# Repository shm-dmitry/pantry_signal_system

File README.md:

This is signal system for pantry.
It will control climate of pantry to smart house.

It will uses autonomous power system
1. car battery on 12v
2. temporary Li-Ion battary on 12v for charging primary battery
3. internal battery (6V..15V) which will used in case of primary and reserve 12V battery discharged. Used to send power alarm to smart house
4. Auto battary hot switch
5. Control over-discharge of all batteries
6. Provide information of current voltage to controller
7. Small current consumption. I plan to charge main battary once per ~6 month. 

It will collect and send next information (incl alarms):
1. Inside flooding alarm
2. Outside flooding alarm
3. Inside humidity level
4. Inside temperature
5. Inside light level
6. Open door alarm
7. Current voltage of all batteries
8. Current battery in use
9. Both 12V batteries discharged alarm 

It will automatically switch on air-drier basing on humidity level

It will have air fan system
1. Manual swotch on
2. Manual swotch off
3. Auto switch off after ~20 minutes

It will send all collected information to smart house system using LoRa channel

Project status

| Hardware | Status |
| --- | --- |
| Supply module | OK |
| Supply module :: Supply controller | OK |
| Logic module :: Flooding sensors | OK |
| Logic module :: Light sensor | OK |
| Logic module :: display | OK |
| Logic module :: humidity and temperature | OK |
| Logic module :: air dryer | OK |
| Logic module :: LoRa transmitter | OK |
| Logic module :: Open door alarm | OK |
| Logic module :: Wakeup button | OK |
| Air fan module | OK |
| LoRa receiver and smart house integration | OK |

| Firmware | Status |
| --- | --- |
| Supply controller | OK |
| Logic controller :: flooding sensors | OK |
| Logic controller :: light sensor | OK |
| Logic controller :: display | OK |
| Logic controller :: humidity and temperature | OK |
| Logic controller :: air dryer | OK |
| Logic controller :: LoRa transmitter | OK |
| Logic controller :: Open door alarm | OK |
| Logic controller :: Wakeup button and deep sleep mode | OK |
| Logic controller :: Integration with supply controller | OK |
| LoRa receiver and smart house integration | OK |

| Board | Status |
| --- | --- |
| Supply board | OK |
| logic module board | OK |
| fan board | OK |
| LoRa Receiver | OK |

| 3D models | Status |
| --- | --- |
| Supply board box | OK |
| Logic model box | OK |
| Air dryer | OK |
| Fan box | OK |
| Fan air intake | OK |
| LoRa receiver box | no |

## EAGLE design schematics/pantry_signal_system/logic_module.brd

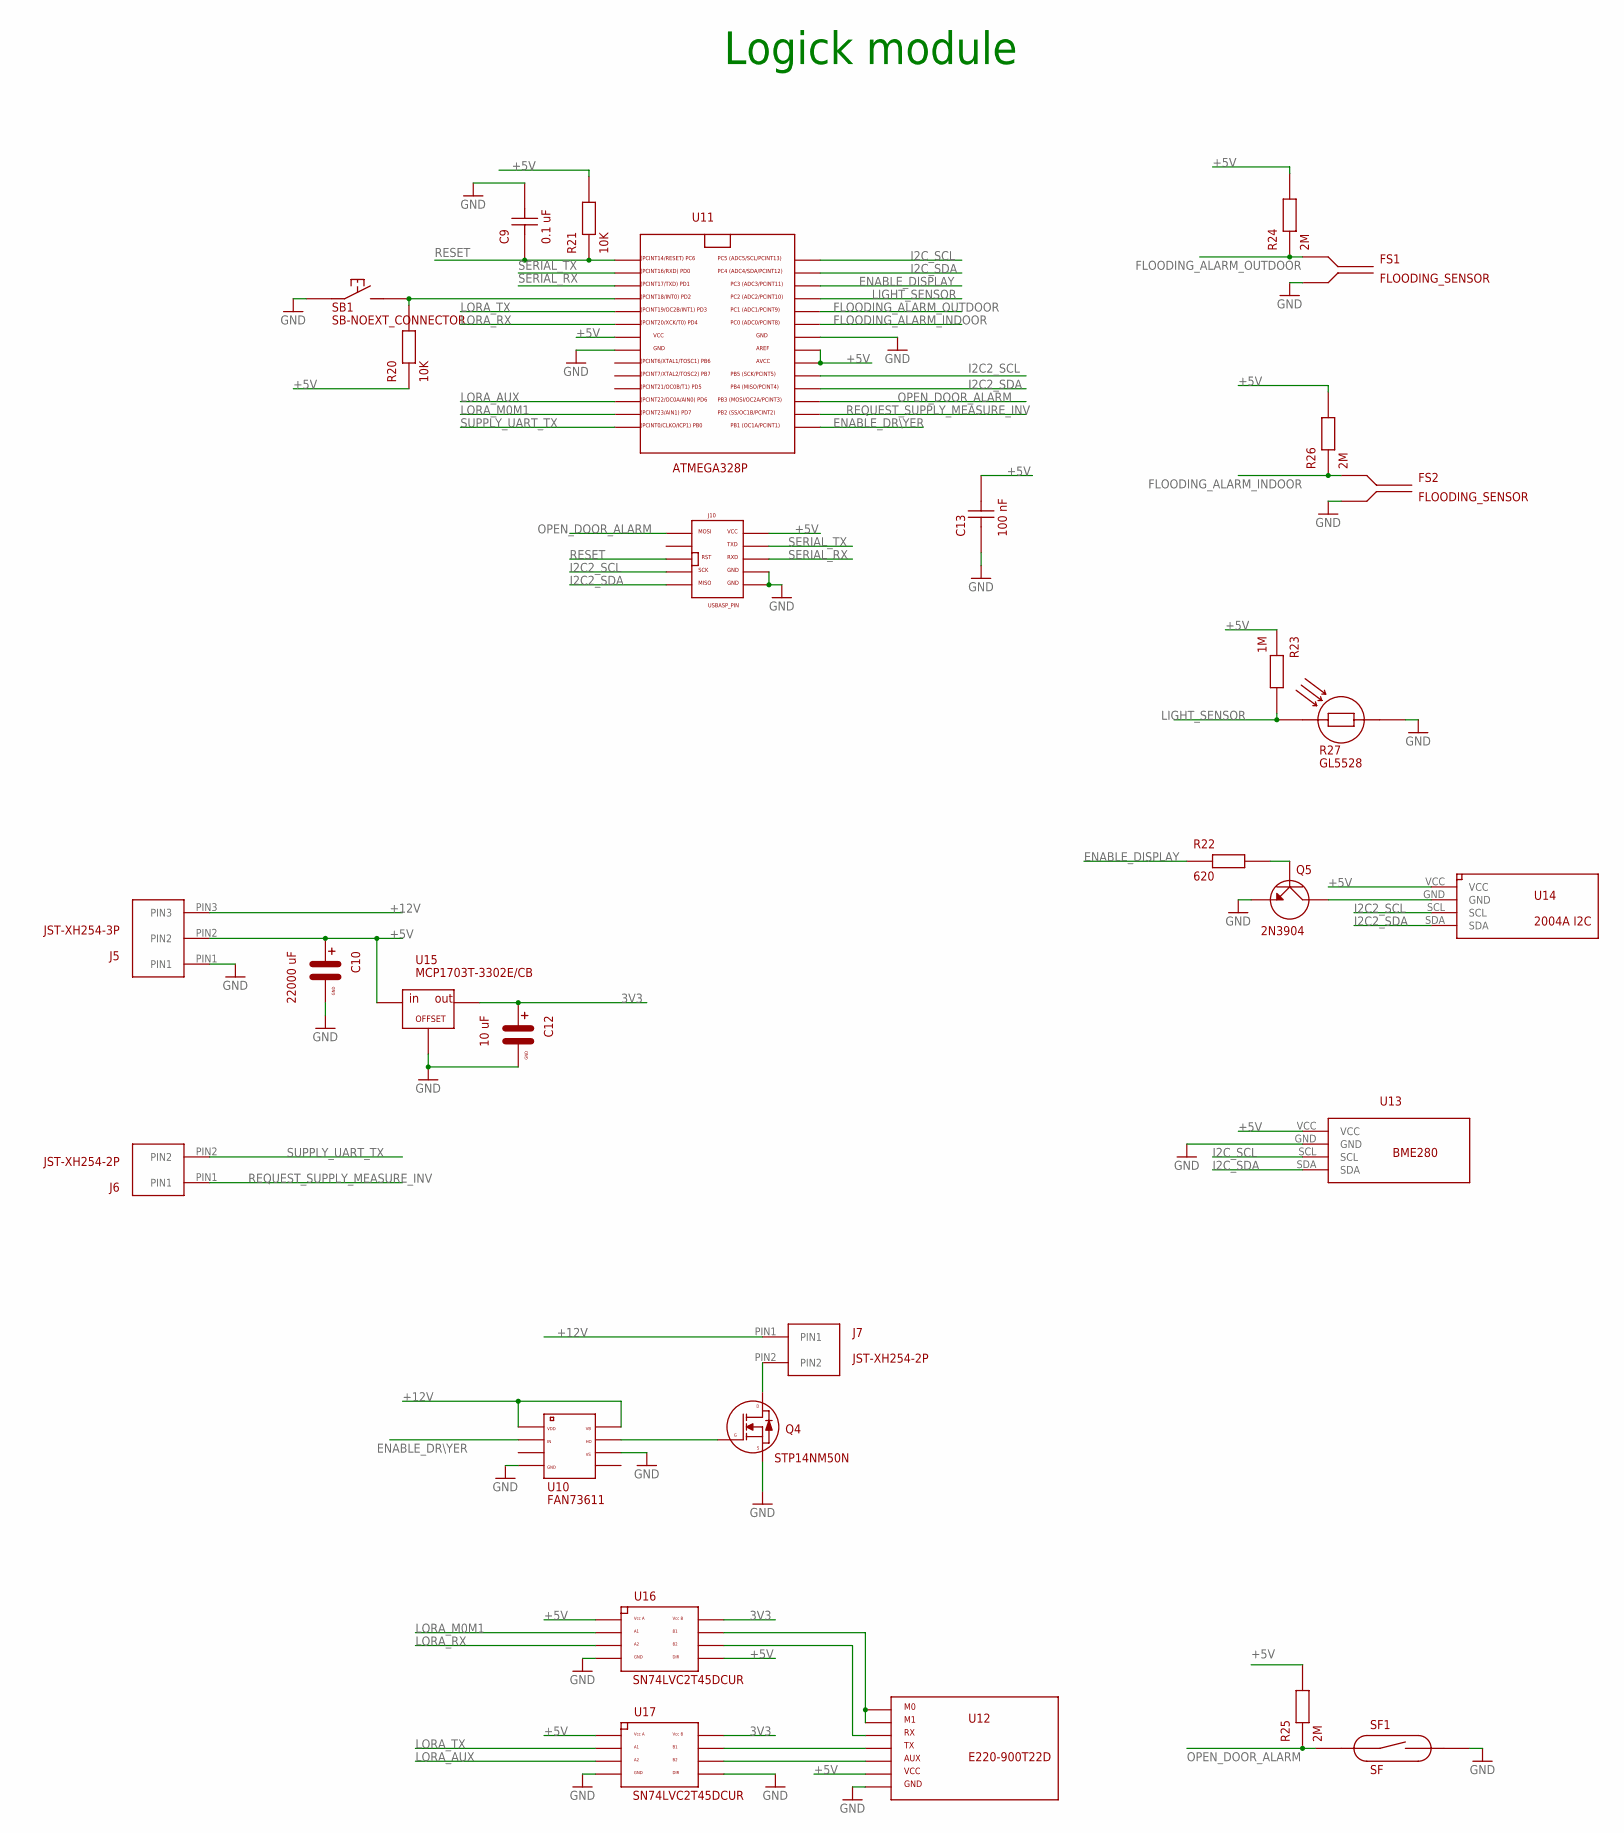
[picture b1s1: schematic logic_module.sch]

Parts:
C9: 0.1 uF; C-1
C10: 22000 uF; C-MINI-5X7
C12: 10 uF; C-MINI-5X7
C13: 100 nF; C-1
FS1, FS2: FLOODING_SENSOR
J5: JST-XH254-3P
J6, J7: JST-XH254-2P
J10: USBASP_PIN
Q4: STP14NM50N; MOSFET_N
Q5: 2N3904; TRANSISTOR
R20, R21: 10K; R
R22: 620; R
R23: 1M; R
R24, R25, R26: 2M; R
R27: GL5528; RF
SB1: SB-NOEXT_CONNECTOR; SB-EXT
SF1: SF
U10: FAN73611; SOIC-8
U11: ATMEGA328P
U12: E220-900T22D; LORA
U13: BME280BME280-CONNECTOR-ONLY; BME280-CONNECTOR-ONLY
U14: 2004A I2C; I2C_DISPLAY
U15: MCP1703T-3302E/CB; SOT-23A
U16, U17: SN74LVC2T45DCUR; VSSOP-8

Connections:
3V3: C12.PLUS (PIN_PLUS), U15.P2 (OUT), U16.P8 (VCCB), U17.P8 (VCCB)
+5V: C10.PLUS (PIN_PLUS), C13.P$2, J5.PIN2, J10.VCC, R20.P$1, R21.P$2, R23.P$1, R24.P$2, R25.P$2, R26.P$2, U11.AREF, U11.AVCC, U11.VCC, U12.VCC, U13.VCC, U14.VCC, U15.P3 (IN), U16.P1 (VCCA), U16.P5 (DIR), U17.P1 (VCCA)
+12V: J5.PIN3, J7.PIN1, U10.P_1 (VDD), U10.P_8 (VB)
ENABLE_DISPLAY: R22.P$1, U11.PC3
ENABLE_DR\YER: U10.P_2 (IN), U11.PB1
FLOODING_ALARM_INDOOR: FS2.P$1, R26.P$1, U11.PC0
FLOODING_ALARM_OUTDOOR: FS1.P$1, R24.P$1, U11.PC1
GND: C9.P$2, C10.MINUS (PIN_GND), C12.MINUS (PIN_GND), C13.P$1, FS1.P$2, FS2.P$2, J5.PIN1, J10.GND, J10.GND1, Q4.S, Q5.E, R27.PIN2, SB1.P$1, SF1.P$2, U10.P_4 (GND), U10.P_6 (VS), U11.GND, U11.GND1, U12.GND, U13.GND, U15.P1 (GND), U16.P4 (GND), U17.P4 (GND), U17.P5 (DIR)
I2C2_SCL: J10.SCK, U11.PB5, U14.SCL
I2C2_SDA: J10.MISO, U11.PB4, U14.SDA
I2C_SCL: U11.PC5, U13.SCL
I2C_SDA: U11.PC4, U13.SDA
LIGHT_SENSOR: R23.P$2, R27.PIN1, U11.PC2
LORA_AUX: U11.PD6, U17.P3 (A2)
LORA_M0M1: U11.PD7, U16.P2 (A1)
LORA_RX: U11.PD4, U16.P3 (A2)
LORA_TX: U11.PD3, U17.P2 (A1)
unnamed: U12.TX, U17.P7 (B1)
unnamed: U12.RX, U16.P6 (B2)
unnamed: U12.AUX, U17.P6 (B2)
unnamed: J7.PIN2, Q4.D
unnamed: Q4.G, U10.P_7 (HO)
unnamed: U12.M0, U12.M1, U16.P7 (B1)
unnamed: Q5.C, U14.GND
unnamed: Q5.B, R22.P$2
unnamed: R20.P$2, SB1.P$2, U11.PD2
OPEN_DOOR_ALARM: J10.MOSI, R25.P$1, SF1.P$1, U11.PB3
REQUEST_SUPPLY_MEASURE_INV: J6.PIN1, U11.PB2
RESET: C9.P$1, J10.RST (RESET), R21.P$1, U11.PC6
SERIAL_RX: J10.RXD, U11.PD1
SERIAL_TX: J10.TXD, U11.PD0
SUPPLY_UART_TX: J6.PIN2, U11.PB0

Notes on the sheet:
Logick module

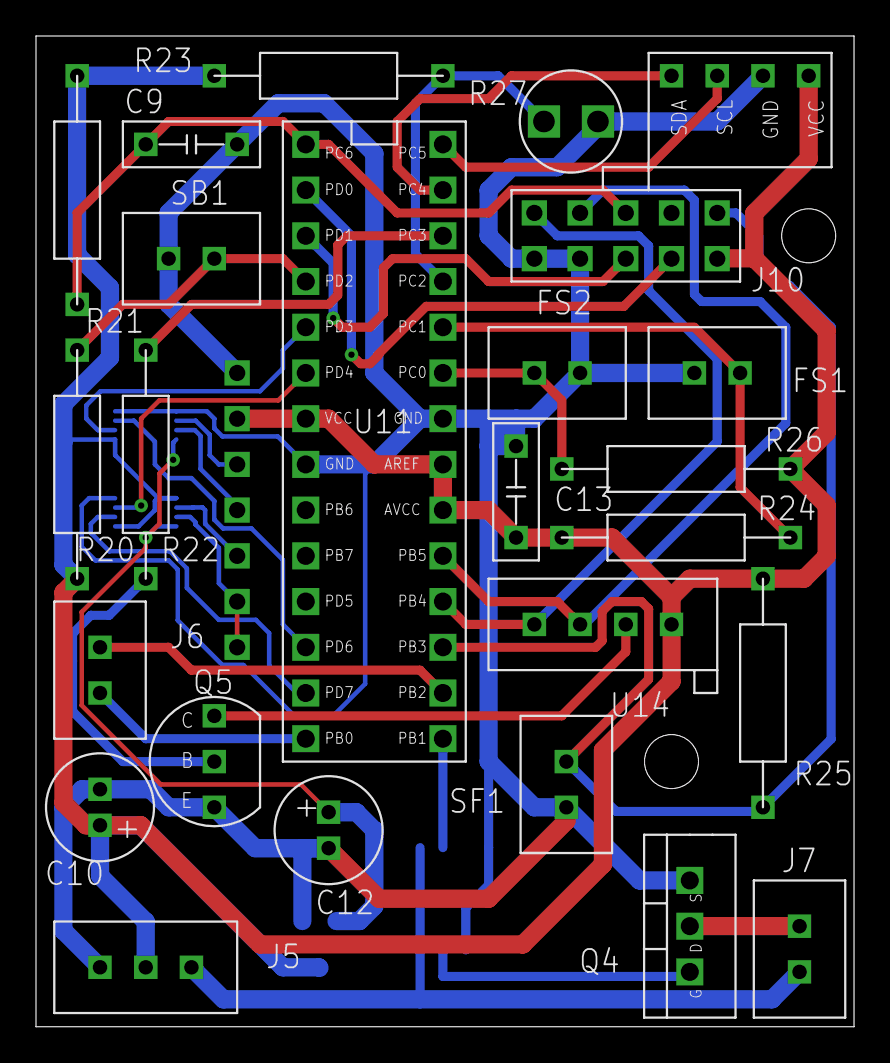
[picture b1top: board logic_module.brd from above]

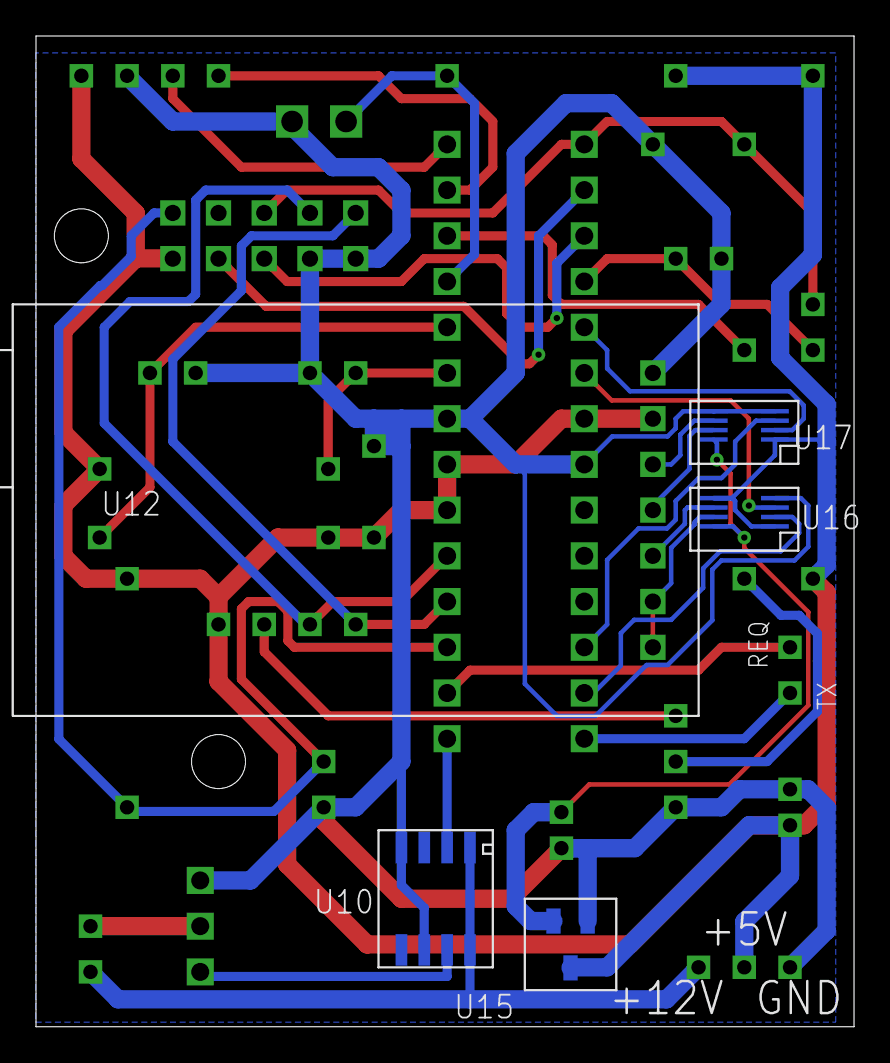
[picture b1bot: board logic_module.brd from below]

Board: 2 copper layers, 45.4 x 55.0 mm, 30 parts (5 on the bottom side), 32 nets.

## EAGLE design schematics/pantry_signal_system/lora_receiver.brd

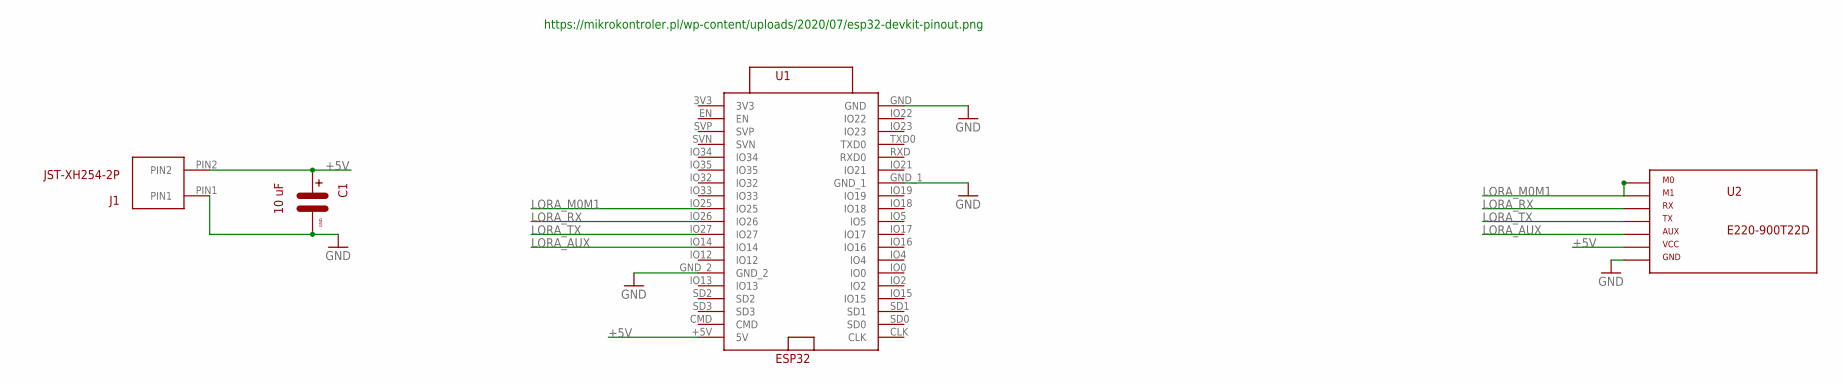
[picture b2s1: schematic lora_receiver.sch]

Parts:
C1: 10 uF; C-MINI-5X7
J1: JST-XH254-2P
U1: ESP32
U2: E220-900T22D; LORA

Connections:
3V3: U1.3V3
+5V: C1.PLUS (PIN_PLUS), J1.PIN2, U1.+5V (5V), U2.VCC
GND: C1.MINUS (PIN_GND), J1.PIN1, U1.GND, U1.GND_1, U1.GND_2, U2.GND
LORA_AUX: U1.IO14, U2.AUX
LORA_M0M1: U1.IO25, U2.M0, U2.M1
LORA_RX: U1.IO26, U2.RX
LORA_TX: U1.IO27, U2.TX

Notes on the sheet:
https://mikrokontroler.pl/wp-content/uploads/2020/07/esp32-devkit-pinout.png

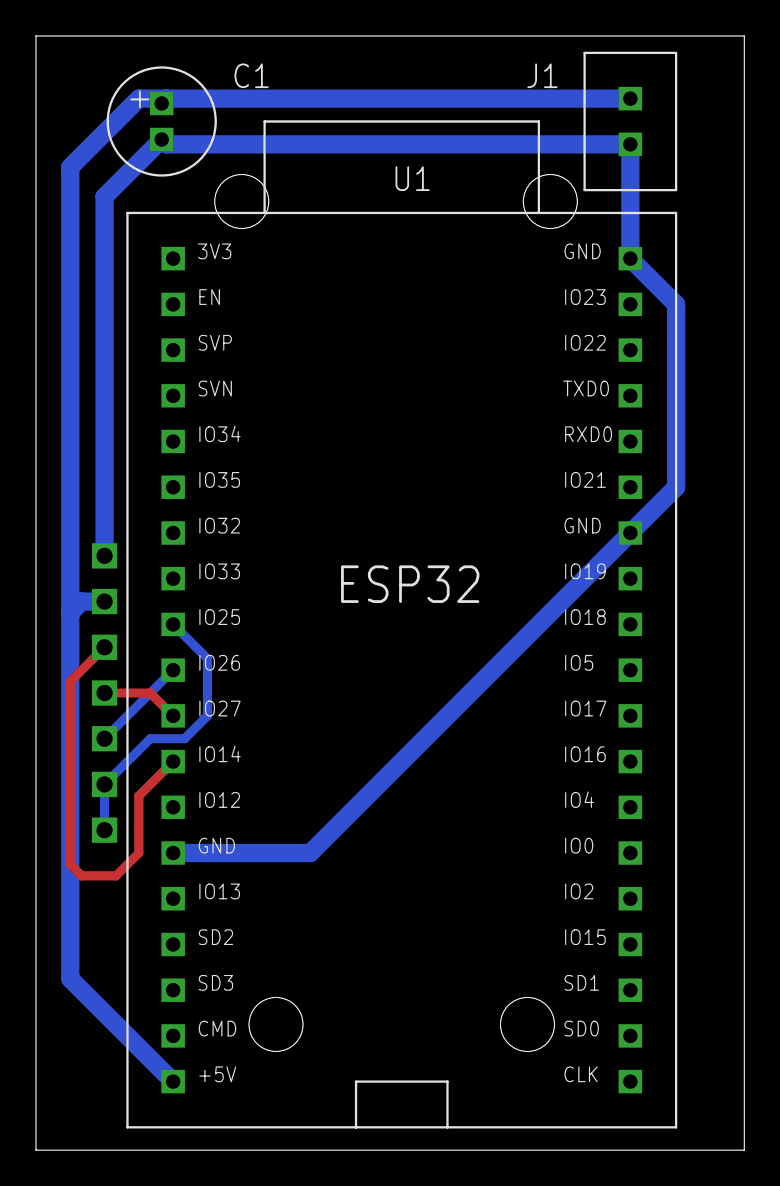
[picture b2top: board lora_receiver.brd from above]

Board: 2 copper layers, 39.4 x 61.9 mm, 4 parts (1 on the bottom side), 6 nets.

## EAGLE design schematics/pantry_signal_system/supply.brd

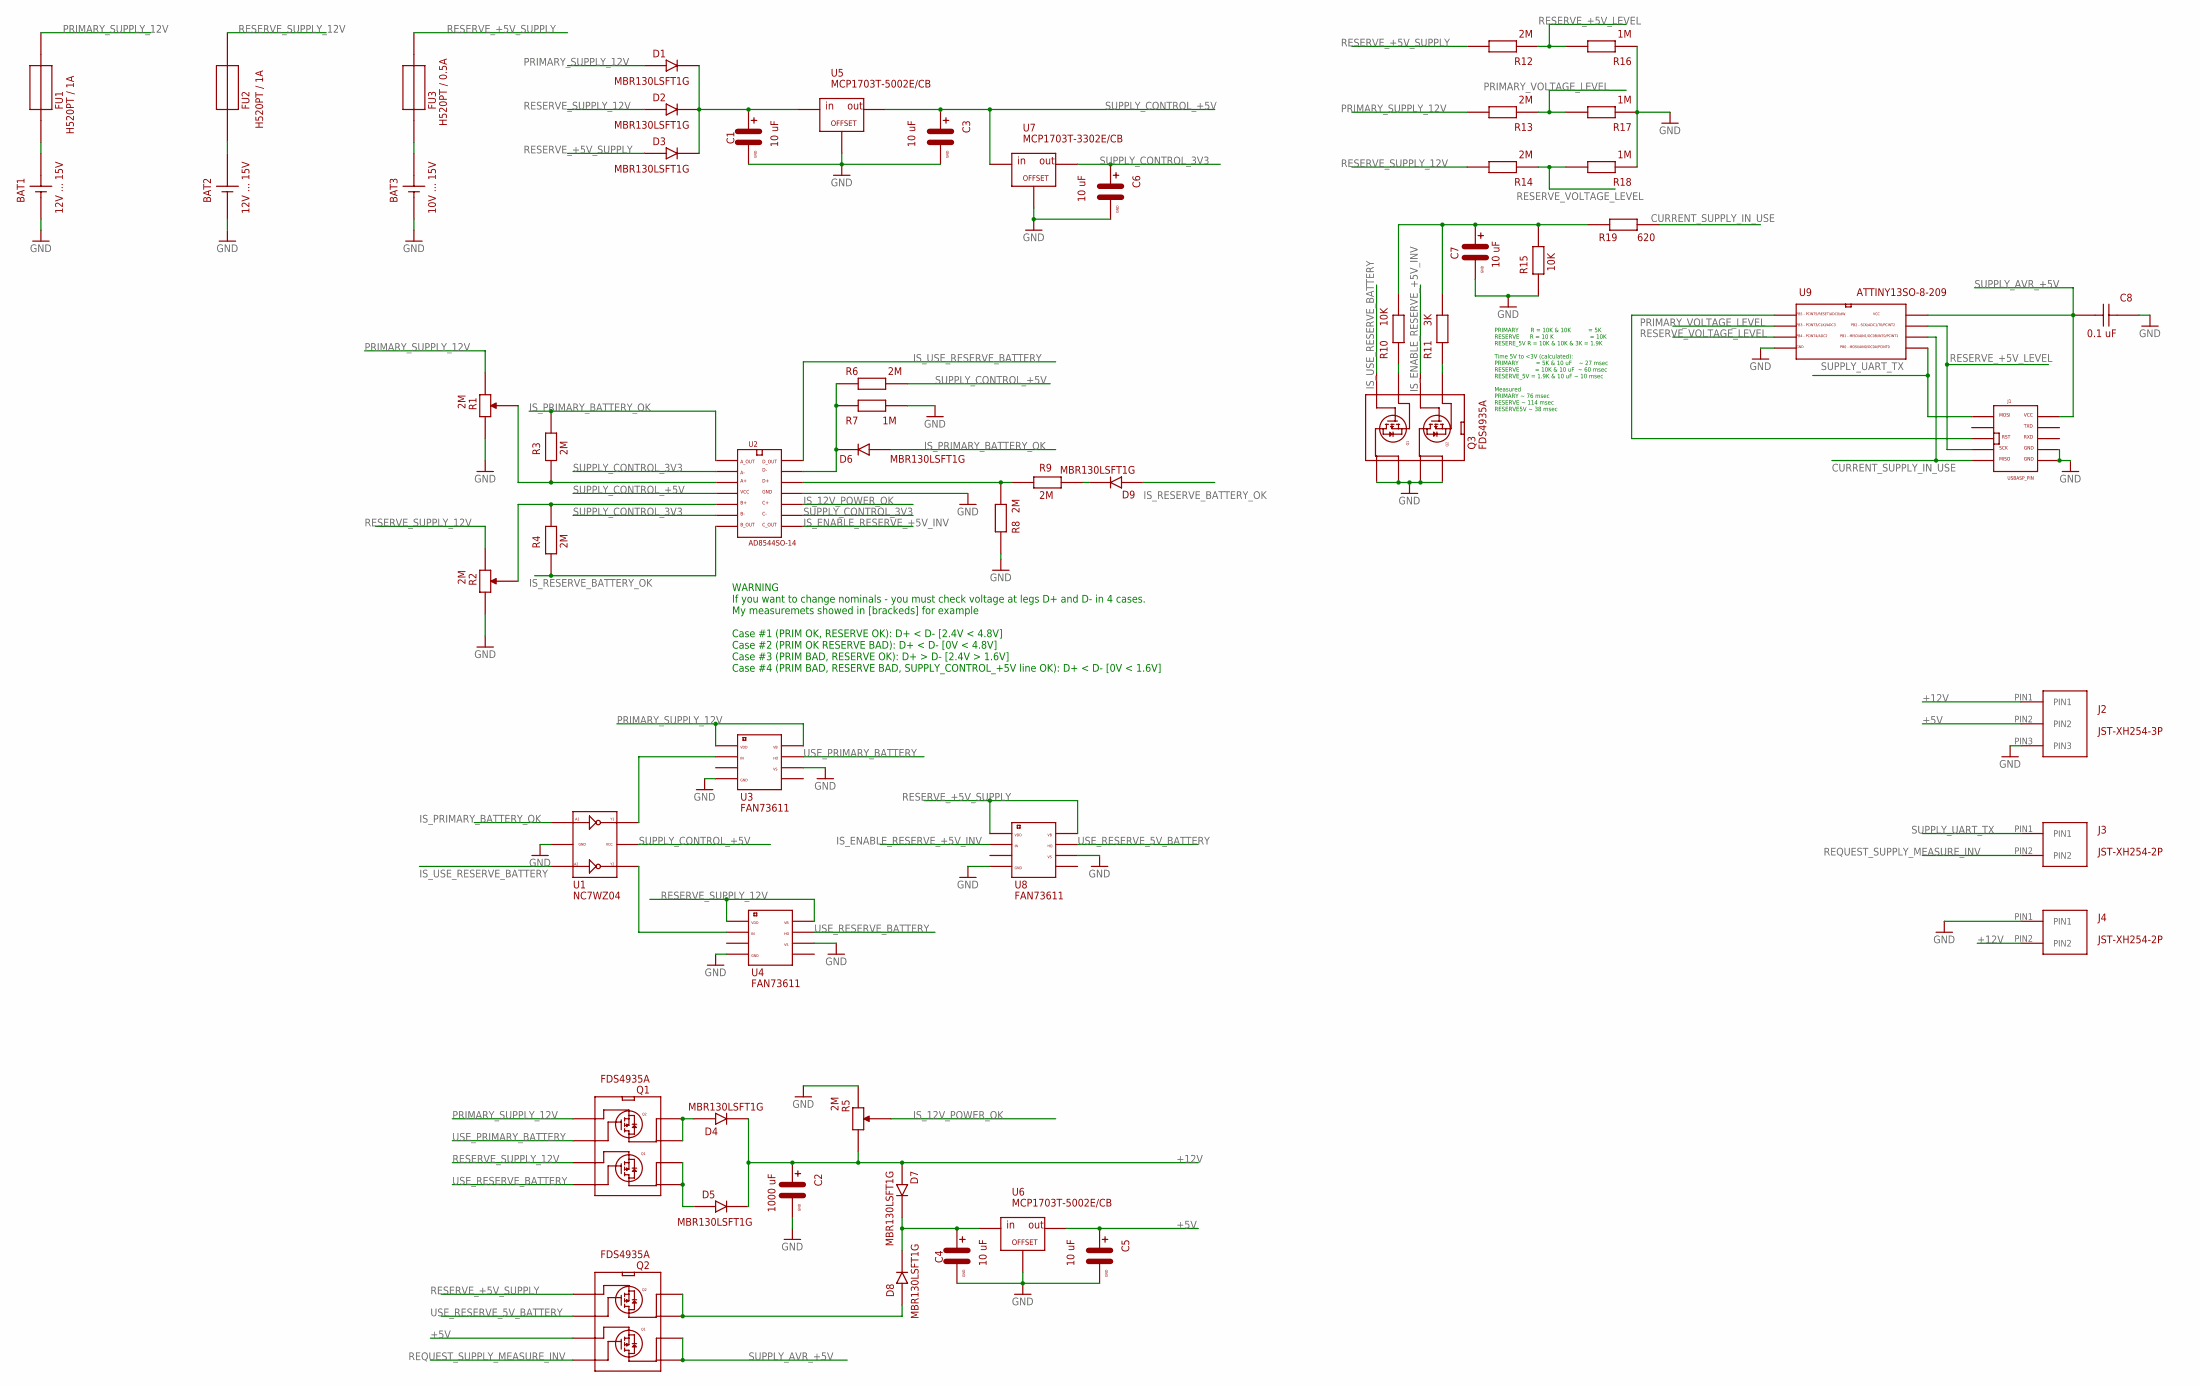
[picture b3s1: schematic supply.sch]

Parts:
BAT1, BAT2: 12V ... 15V; BATTERY
BAT3: 10V ... 15V; BATTERY
C1, C3, C4, C5, C6, C7: 10 uF; C-MINI-5X7
C2: 1000 uF; C
C8: 0.1 uF; C-1
D1, D2, D3, D4, D5, D6, D7, D8, D9: MBR130LSFT1G; D-SOD-123FL
FU1, FU2: H520PT / 1A; FU
FU3: H520PT / 0.5A; FU
J1: USBASP_PIN
J2: JST-XH254-3P
J3, J4: JST-XH254-2P
Q1, Q2, Q3: FDS4935A; SO-8
R1, R2, R5: 2M; RD-3296W-1-205LF
R3, R4, R6, R8, R9, R12, R13, R14: 2M; R
R7, R16, R17, R18: 1M; R
R10, R15: 10K; R
R11: 3K; R
R19: 620; R
U1: NC7WZ04; SC70
U2: AD8544SO-14; SO-14
U3, U4, U8: FAN73611; SOIC-8
U5, U6: MCP1703T-5002E/CB; SOT-23A
U7: MCP1703T-3302E/CB; SOT-23A
U9: ATTINY13SO-8-209; SO-8-209

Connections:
+5V: C5.PLUS (PIN_PLUS), J2.PIN2, Q2.P3 (S1), U6.P2 (OUT)
+12V: C2.PIN_PLUS, D4.CATHODE, D5.CATHODE, D7.ANODE, J2.PIN1, J4.PIN2, R5.P2
BAT1: BAT1.PLUS, FU1.P$1
BAT2: BAT2.PLUS, FU2.P$1
BAT3: BAT3.PLUS, FU3.P$1
CURRENT_SUPPLY_IN_USE: J1.MISO, R19.P$2, U9.P6 (PB1)
GND: BAT1.MINUS, BAT2.MINUS, BAT3.MINUS, C1.MINUS (PIN_GND), C2.PIN_GND, C3.MINUS (PIN_GND), C4.MINUS (PIN_GND), C5.MINUS (PIN_GND), C6.MINUS (PIN_GND), C7.MINUS (PIN_GND), C8.P$2, J1.GND, J1.GND1, J2.PIN3, J4.PIN1, Q3.P5 (D11), Q3.P6 (D12), Q3.P7 (D21), Q3.P8 (D22), R1.P2, R2.P2, R5.P1, R7.P$1, R8.P$2, R15.P$1, R16.P$1, R17.P$1, R18.P$1, U1.P2 (GND), U2.P11 (GND), U3.P_4 (GND), U3.P_6 (VS), U4.P_4 (GND), U4.P_6 (VS), U5.P1 (GND), U6.P1 (GND), U7.P1 (GND), U8.P_4 (GND), U8.P_6 (VS), U9.P4 (GND)
IS_12V_POWER_OK: R5.P3, U2.P10 (C+)
IS_ENABLE_RESERVE_+5V_INV: Q3.P2 (G2), U2.P8 (C_OUT), U8.P_2 (IN)
IS_PRIMARY_BATTERY_OK: D6.ANODE, R3.P$2, U1.P1 (A1), U2.P1 (A_OUT)
IS_RESERVE_BATTERY_OK: D9.ANODE, R4.P$1, U2.P7 (B_OUT)
IS_USE_RESERVE_BATTERY: Q3.P4 (G1), U1.P3 (A2), U2.P14 (D_OUT)
unnamed: C1.PLUS (PIN_PLUS), D1.CATHODE, D2.CATHODE, D3.CATHODE, U5.P3 (IN)
unnamed: D6.CATHODE, R6.P$2, R7.P$2, U2.P13 (D-)
unnamed: R1.P3, R3.P$1, U2.P3 (A+)
unnamed: C4.PLUS (PIN_PLUS), D7.CATHODE, D8.CATHODE, U6.P3 (IN)
unnamed: R2.P3, R4.P$2, U2.P5 (B+)
unnamed: R8.P$1, R9.P$1, U2.P12 (D+)
unnamed: D4.ANODE, Q1.P7 (D21), Q1.P8 (D22)
unnamed: D5.ANODE, Q1.P5 (D11), Q1.P6 (D12)
unnamed: J1.RST (RESET), U9.P1 (PB5)
unnamed: U1.P6 (Y1), U3.P_2 (IN)
unnamed: U1.P4 (Y2), U4.P_2 (IN)
unnamed: Q3.P3 (S1), R10.P$1
unnamed: D8.ANODE, Q2.P7 (D21), Q2.P8 (D22)
unnamed: Q3.P1 (S2), R11.P$1
unnamed: D9.CATHODE, R9.P$2
unnamed: C7.PLUS (PIN_PLUS), R10.P$2, R11.P$2, R15.P$2, R19.P$1
PRIMARY_SUPPLY_12V: D1.ANODE, FU1.P$2, Q1.P1 (S2), R1.P1, R13.P$2, U3.P_1 (VDD), U3.P_8 (VB)
PRIMARY_VOLTAGE_LEVEL: R13.P$1, R17.P$2, U9.P2 (PB3)
REQUEST_SUPPLY_MEASURE_INV: J3.PIN2, Q2.P4 (G1)
RESERVE_+5V_LEVEL: J1.SCK, R12.P$1, R16.P$2, U9.P7 (PB2)
RESERVE_+5V_SUPPLY: D3.ANODE, FU3.P$2, Q2.P1 (S2), R12.P$2, U8.P_1 (VDD), U8.P_8 (VB)
RESERVE_SUPPLY_12V: D2.ANODE, FU2.P$2, Q1.P3 (S1), R2.P1, R14.P$2, U4.P_1 (VDD), U4.P_8 (VB)
RESERVE_VOLTAGE_LEVEL: R14.P$1, R18.P$2, U9.P3 (PB4)
SUPPLY_AVR_+5V: C8.P$1, J1.VCC, Q2.P5 (D11), Q2.P6 (D12), U9.P8 (VCC)
SUPPLY_CONTROL_3V3: C6.PLUS (PIN_PLUS), U2.P2 (A-), U2.P6 (B-), U2.P9 (C-), U7.P2 (OUT)
SUPPLY_CONTROL_+5V: C3.PLUS (PIN_PLUS), R6.P$1, U1.P5 (VCC), U2.P4 (VCC), U5.P2 (OUT), U7.P3 (IN)
SUPPLY_UART_TX: J1.MOSI, J3.PIN1, U9.P5 (PB0)
USE_PRIMARY_BATTERY: Q1.P2 (G2), U3.P_7 (HO)
USE_RESERVE_5V_BATTERY: Q2.P2 (G2), U8.P_7 (HO)
USE_RESERVE_BATTERY: Q1.P4 (G1), U4.P_7 (HO)

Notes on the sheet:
PRIMARY R = 10K & 10K = 5K RESERVE R = 10 K = 10K RESERE_5V R = 10K & 10K & 3K = 1.9K Time 5V to <3V (calculated): PRIMARY = 5K & 10 uF ~ 27 msec RESERVE = 10K & 10 uF ~ 60 msec RESERVE_5V = 1.9K & 10 uF ~ 10 msec Measured PRIMARY ~ 76 msec RESERVE ~ 114 msec RESERVE5V ~ 38 msec
WARNING If you want to change nominals - you must check voltage at legs D+ and D- in 4 cases. My measuremets showed in [brackeds] for example Case #1 (PRIM OK, RESERVE OK): D+ < D- [2.4V < 4.8V] Case #2 (PRIM OK RESERVE BAD): D+ < D- [0V < 4.8V] Case #3 (PRIM BAD, RESERVE OK): D+ > D- [2.4V > 1.6V]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

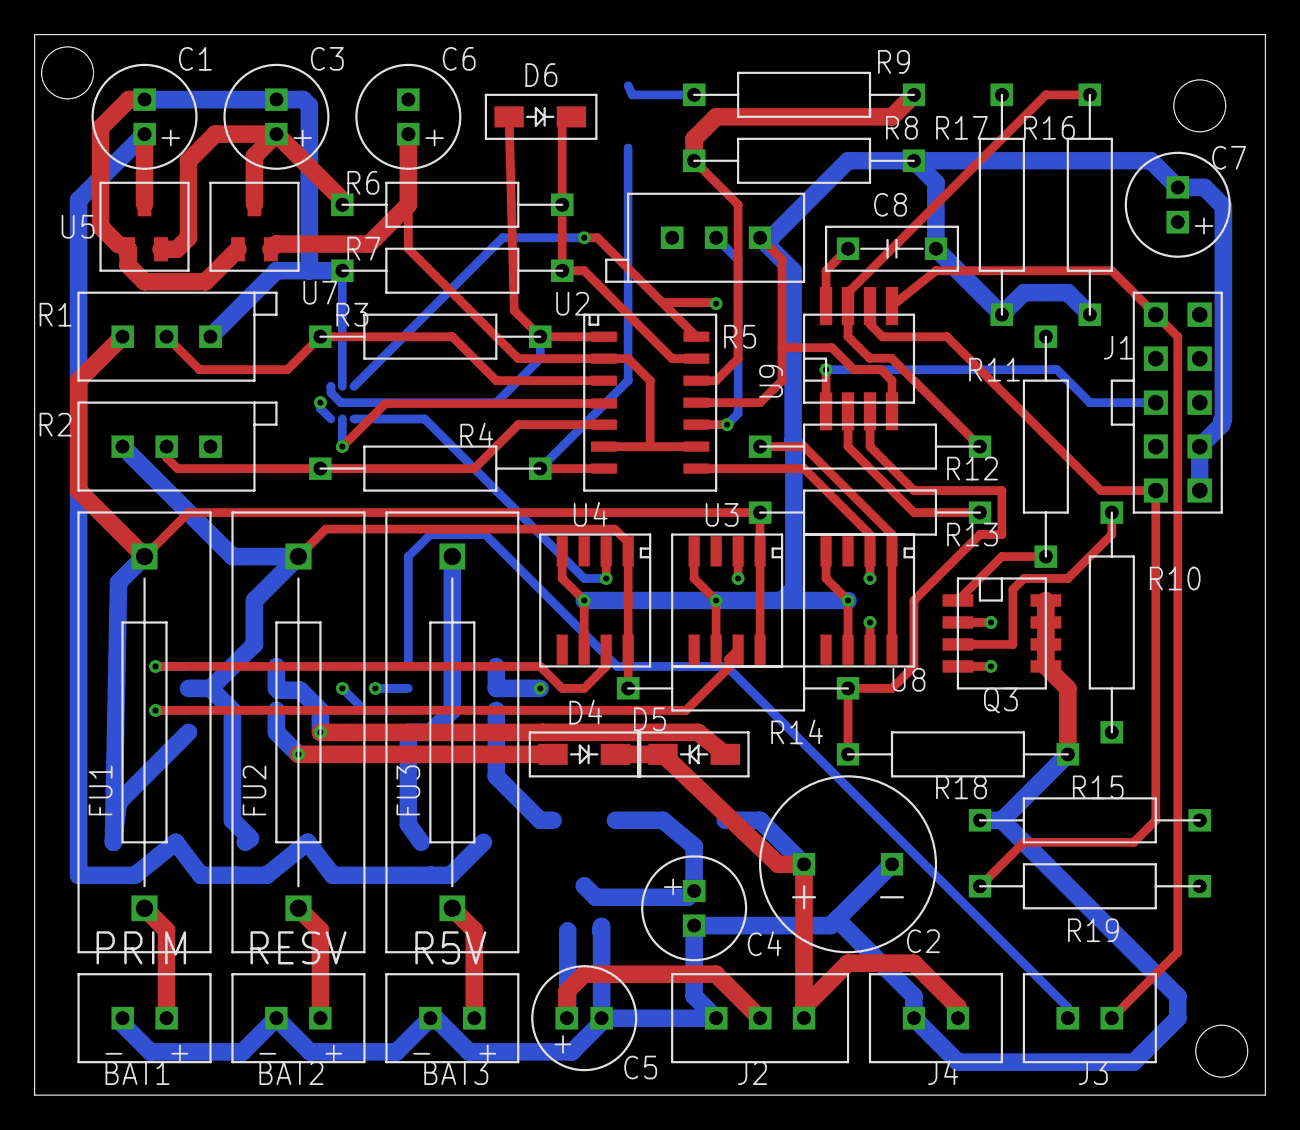
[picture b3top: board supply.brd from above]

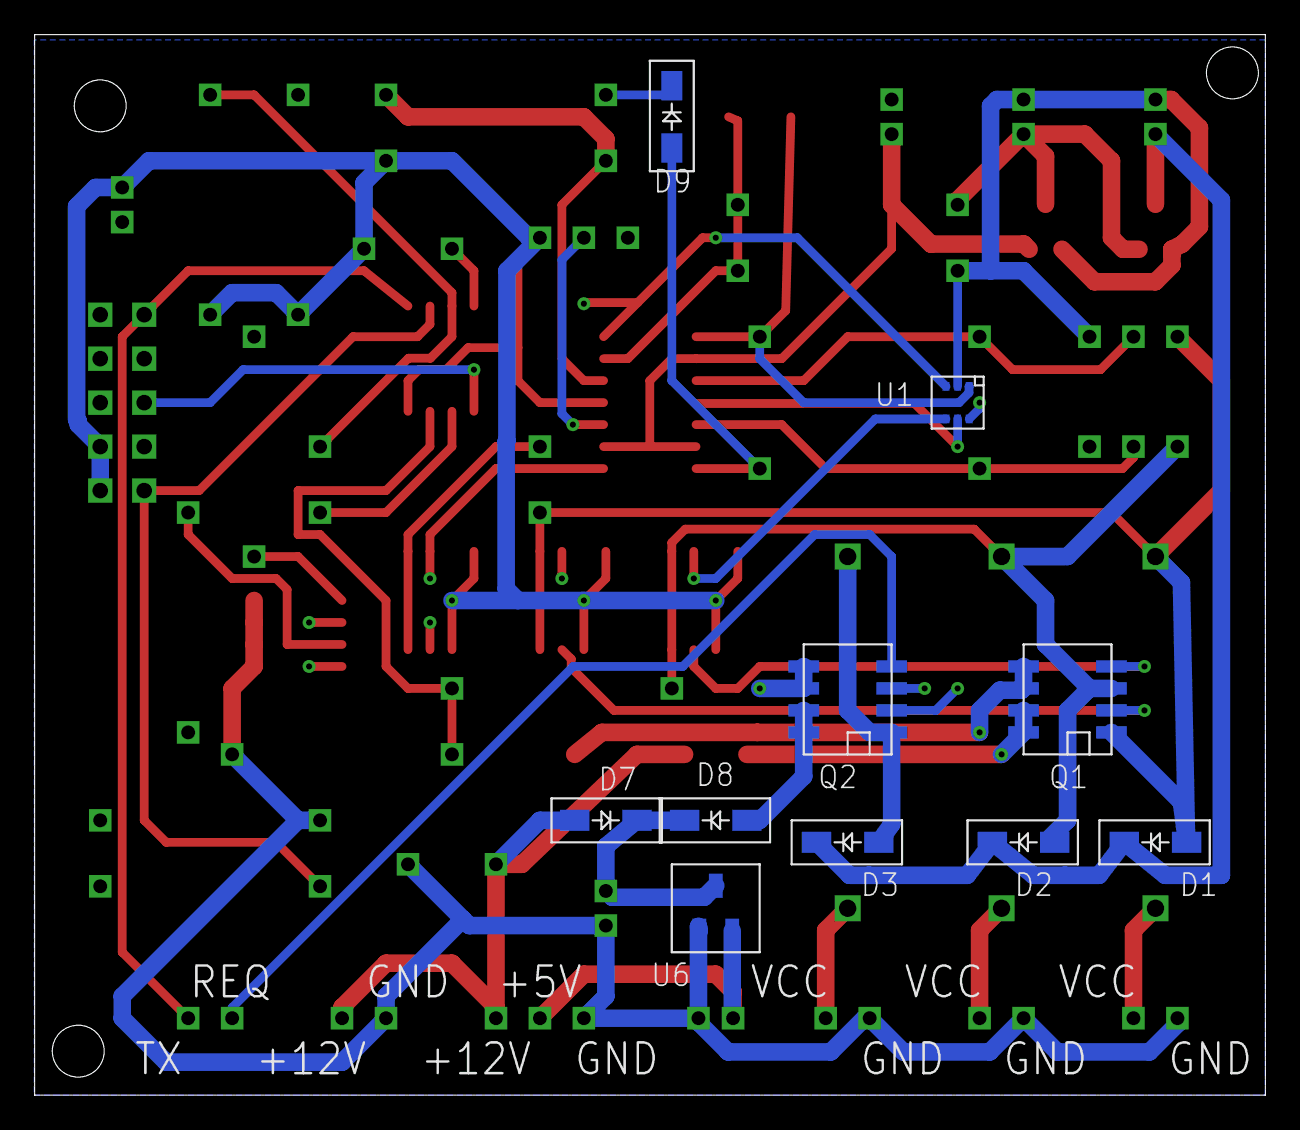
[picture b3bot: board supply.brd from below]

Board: 4 copper layers, 71.1 x 61.3 mm, 58 parts (10 on the bottom side), 42 nets.

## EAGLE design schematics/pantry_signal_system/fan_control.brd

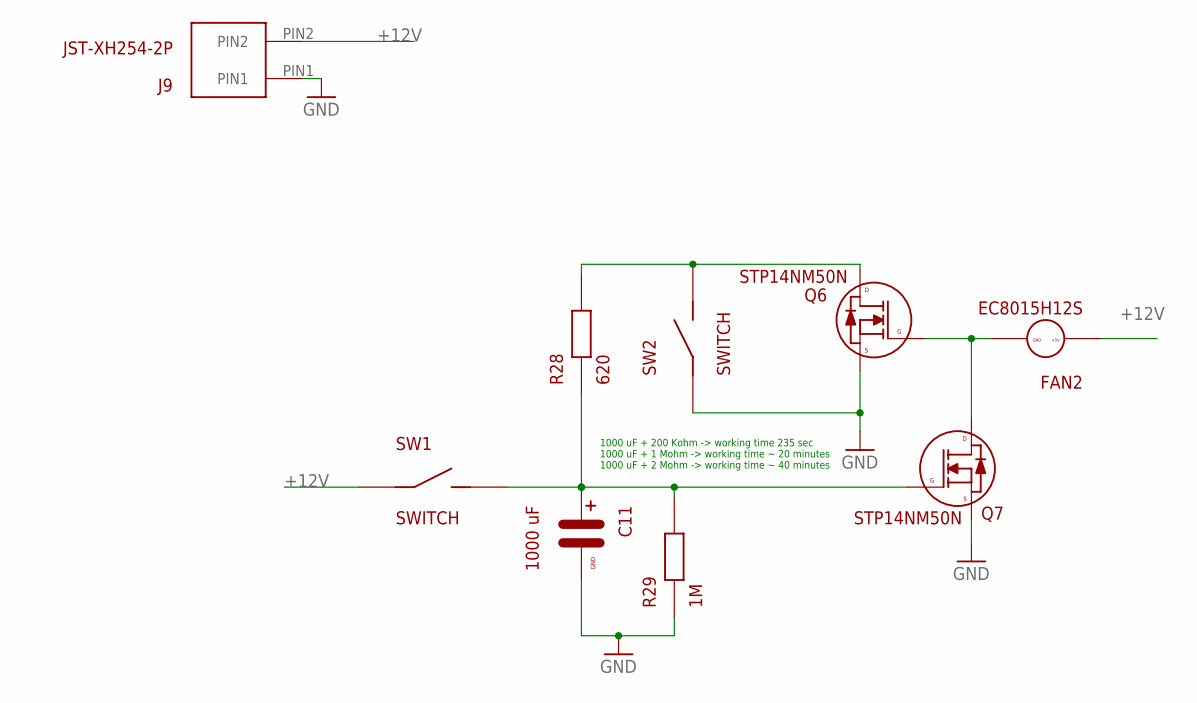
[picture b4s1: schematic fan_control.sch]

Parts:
C11: 1000 uF; C
FAN2: EC8015H12S; FAN_5V
J9: JST-XH254-2P
Q6, Q7: STP14NM50N; MOSFET_N
R28: 620; R
R29: 1M; R
SW1, SW2: SWITCH

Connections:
+12V: FAN2.VCC, J9.PIN2, SW1.P$1
GND: C11.PIN_GND, J9.PIN1, Q6.S, Q7.S, R29.P$1, SW2.P$1
unnamed: FAN2.GND, Q6.G, Q7.D
unnamed: C11.PIN_PLUS, Q7.G, R28.P$1, R29.P$2, SW1.P$2
unnamed: Q6.D, R28.P$2, SW2.P$2

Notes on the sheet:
1000 uF + 200 Kohm -> working time 235 sec 1000 uF + 1 Mohm -> working time ~ 20 minutes 1000 uF + 2 Mohm -> working time ~ 40 minutes

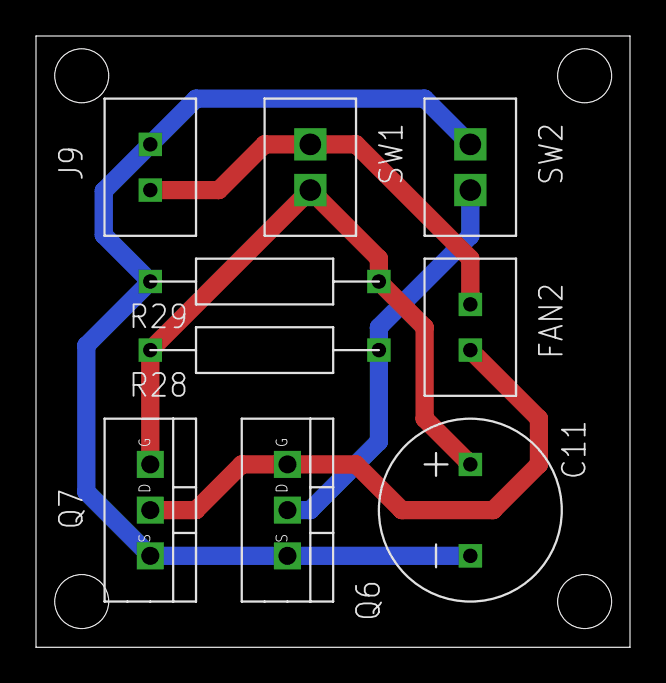
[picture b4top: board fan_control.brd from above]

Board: 2 copper layers, 33.0 x 34.0 mm, 9 parts (0 on the bottom side), 5 nets.

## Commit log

2021-11-15 Initial
2021-11-15 Start creating schema
2021-11-15 Initial schema for supply subsystem
2021-11-16 Initial schema for logic module
2021-11-16 Initial schema for fan system
2021-11-16 added some nominals
2021-11-20 Added +5V reserve supply and auto-enable schema wich switched it on when primary and reserve 12V supply discharged
2021-11-20 Update library
2021-11-20 Added nominals for air fan
2021-11-20 Fixed comment for working time of air fan
2021-11-21 Start writing firmware for logic module
2021-11-21 open door alarm
2021-11-25 changed mosfet drivers to FAN73611
2021-11-25 Added lora-send code
2021-11-25 LoRa - added configuration, and wakeup-sleep-mode
2021-12-02 3D model for SOIC8-chips adapter
2021-12-03 Finalized debug model for SOIC8 chips
2021-12-03 Added model for SOC32A debug adapter (bottom side)
2021-12-03 added topside model for SOC23A debug adapter
2021-12-09 Air drier schema works
2021-12-10 Lora module FW and HW works. Encrypted connection betweed modules estabilished
2021-12-11 Added firmware for supply module (not tested yet)
2021-12-12 Display driver and schema ready
2021-12-12 Light sensor is ready now
2021-12-12 Start working under supply schema
2021-12-12 Added programmer connector for ATTiny
2021-12-13 Added integration with supply avr module (not tested yet)
2022-01-12 Working under supplu control
2022-01-12 Continue working under supply control schematics. Changed N-channel mosfets to P-channel mosfets. Small changes in logic control module
2022-01-15 Continue working under supply schematics and supply controller firmware
2022-01-15 actual library
2022-01-16 working under supply schematics. I think I solved problem with 'current battery in use' signal reading
2022-01-18 and another iteration for suplly avr data reading
2022-01-25 Supply controller schematics and firmware ready
2022-01-26 working under supply schematics
2022-01-31 I finished supply control schematics
2022-02-01 start working under wakeup button and deep sleep mode
2022-02-01 Initial deepsleep impl
2022-02-02 1. BME280 works fine. 2. I have problem with I2C bus when display connected, but unpowerd. I will investigate this problem
2022-02-03 Added 3D model of air dryer
2022-02-03 renamed stl file
2022-02-03 remove deleted file
2022-02-08 Try to fix problem with I2C bus and display module
2022-02-08 PINs in source code assigned as in schematics
2022-02-09 wakeup button, deepsleep & display works fine
2022-02-09 ADded lora receiver schema
2022-02-09 Start project LoRa receiver
2022-02-10 lora receiver - finished ESP32 firmware (not tested yet)
2022-02-10 added secret header file to gitignore to ensure I will not push it later
2022-02-10 move secrets to one file
2022-02-10 exclude new secrets file from git
2022-02-10 Fix problem with signal level 3V3 <-> 5V for lora
2022-02-11 Preparing primary schema for creating board - all packages setup
2022-02-13 Changed LoRa Receiver schematics to use level converter modules
2022-02-13 Added board for LoRa receiver
2022-02-13 Added FAN Control board
2022-02-13 Added Logic Module board
2022-02-13 Added supply board
2022-02-14 Boards checked, some packages changed, library synced with this project
2022-02-14 I submited order for this boards....
2022-02-14 Fixed issue in air dryer container 3D model
2022-02-14 air fan income - initial version, I will reduce it's size later
2022-02-15 Air Fan Income redesigned
2022-02-15 Added Air Fan Outcome 3D model
2022-03-03 3D models for air income and air dryer
2022-03-19 1. Fixed issues in boards and firmwares
2022-03-19 Actual board
2022-03-22 Added 3D Models for boxes
2022-04-04 Preparing to assemble device
2022-04-04 Changes in library
2022-04-04 Fixed issue with connection between supply and logic module
2022-04-20 Changes in schematics, changes in source code. Current version works too, but I changed boards to fix some possible errors
2022-04-20 changed gitignore to ensure my private keys didnt pushed
2022-04-20 Secrets moved to another un-tracked header file
2022-06-24 Debugging logic module firmware, estabilishing LoRa connection....
2022-07-01 Firmware for logic-control module finished
2022-07-01 Capacitor nominal changed in logic-module to fix problem with chip restart when LoRa sends data with high current consumption
2022-07-20 working under 3d models
2022-07-25 working under 3D model
2022-07-25 Changes in 3D model
2022-12-06 Changed 3D models to actuall printed, changed firmware to actually flushed
2024-03-07 project finished
2024-10-17 save latest changes before starting v2
2024-10-25 pss v2 board
2024-10-25 fan switch schema rewrited to kicad
